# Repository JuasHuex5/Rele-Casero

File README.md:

# Rele Casero

Autor : Demian David Ramirez

---
# **Descripción**

Este proyecto tiene la finalidad de poder recrear un módulo Relé funcional para accionar un dispositivo electrónico que opera a un voltaje mucho mayor mediante una señal digital proveniente de un microcontrolador programable.
Un ejemplo concreto sería encender un foco, o iniciar una máquina más grande que funciona a 220v.

# **Funcionamiento**

El Esp32 recibe una señal inalámbrica y envía una señal eléctrica con dirección al relé. El sistema es separado por un optoacoplador el cual transmite esa señal sin comprometer al microcontrolador. El transistor se conecta en modo saturación para entregar el voltaje necesario para encender el relé.

# **Justificación de componentes**

### ESP32:
Este microcontrolador permite el fácil control de componentes por señales electrónicas, contando con la capacidad de comunicarse inalámbricamente.

### Relé:
Permite que una señal de menor intensidad encienda un dispositivo de mayor voltaje.

### Optoacoplador:
Aísla dos partes del circuito para evitar que un voltaje mayor queme la parte de bajo voltaje.

### Transistor:
El Relé sólo recibirá corriente cuando el Transistor permite el paso(Como medida preventiva para asegurar el curso correcto de la corriente).

# Analisis Economico
### Materiales

| Componente | Precio |
| ------------- | ------------- |
| ESP32 C3 super mini | 8500 |
| Relé | 1800  |
| 4n25(Optoacoplador) | 3844 |
|2n2222(Transistor) | 200 |
| XL6009 | 3608 - 2990 |
|Placa de cobre|880|

Precio Final:18214

# ESQUEMATICO

# PCB

# Objetivo
Se realiza este proyecto con la finalidad de poder armar un modulo Relay desde casa, ya que los que se encuentran en el mercado son mucho mas costosos que montandolo de manera casera.

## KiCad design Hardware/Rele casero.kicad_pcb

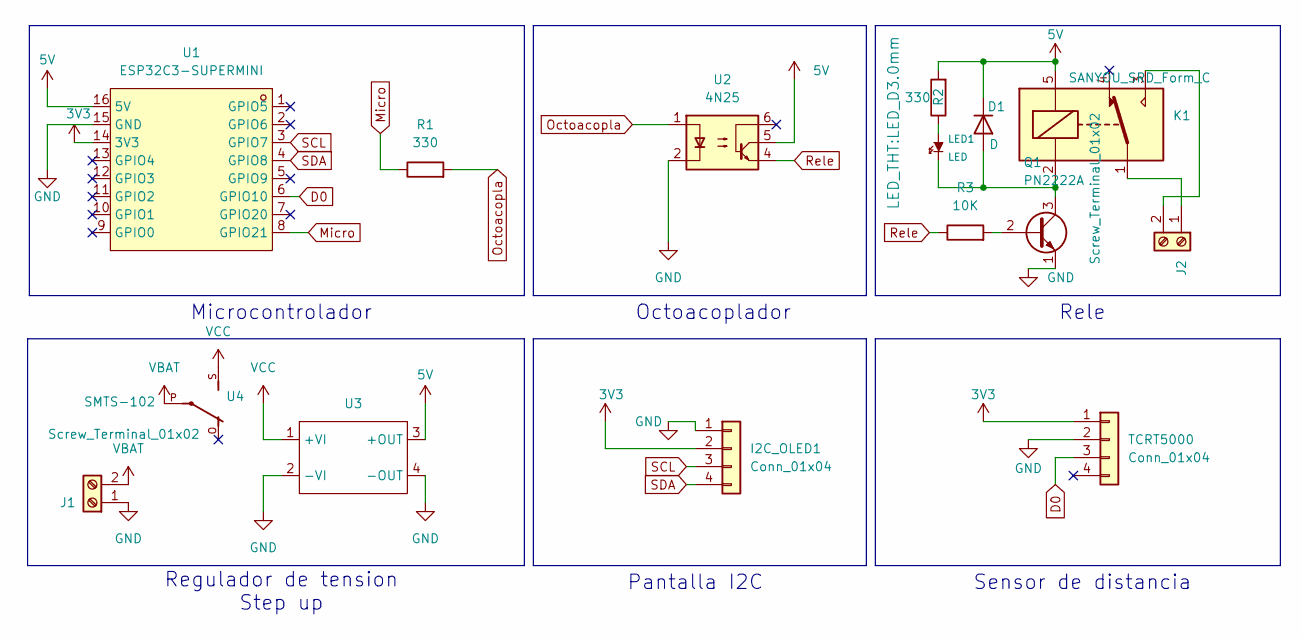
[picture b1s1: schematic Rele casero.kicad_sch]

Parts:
D1: D; D_A-405_P10.16mm_Horizontal
I2C_OLED1: Conn_01x04; PinSocket_1x04_P2.54mm_Vertical
J1, J2: Screw_Terminal_01x02; TerminalBlock_Phoenix_MKDS-1,5-2-5.08_1x02_P5.08mm_Horizont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
K1: SANYOU_SRD_Form_C; Relay_SPDT_SANYOU_SRD_Series_Form_C
LED1: LED; LED_D3.0mm
Q1: PN2222A; TO-92_Inline
R1, R2: 330; R_Axial_DIN0204_L3.6mm_D1.6mm_P7.62mm_Horizontal
R3: 10K; R_Axial_DIN0204_L3.6mm_D1.6mm_P7.62mm_Horizontal
TCRT5000: Conn_01x04; PinSocket_1x04_P2.54mm_Vertical
U1: ESP32C3-SUPERMINI; COMM-SMD_16P-L22.5-W18.0-P2.54-TL; MPN ESP32C3-SuperMini; LCSC Part C9900147397
U2: 4N25; DIP-6_W7.62mm
U3: MT3608-Module
U4: SMTS-102

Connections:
3V3: I2C_OLED1.2, TCRT5000.1, U1.14 (3V3)
5V: D1.1 (K), K1.5, R2.2, U1.16 (5V), U2.5, U3.3 (+OUT)
D0: TCRT5000.3, U1.6 (GPIO10)
GND: I2C_OLED1.1, J1.1, Q1.1 (E), TCRT5000.2, U1.15 (GND), U2.2, U3.2 (-VI), U3.4 (-OUT)
Micro: R1.1, U1.8 (GPIO21)
unnamed: D1.2 (A), K1.2, LED1.2 (K), Q1.3 (C)
unnamed: J2.1, K1.1
unnamed: J2.2, K1.3
unnamed: LED1.1 (A), R2.1
unnamed: Q1.2 (B), R3.2
Octoacopla: R1.2, U2.1
Rele: R3.1, U2.4
SCL: I2C_OLED1.3, U1.3 (GPIO7)
SDA: I2C_OLED1.4, U1.4 (GPIO8)
VBAT: J1.2, U4.P
VCC: U3.1 (+VI), U4.S

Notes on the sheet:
Microcontrolador
Regulador de tension Step up
Pantalla I2C
Sensor de distancia
Octoacoplador
Rele

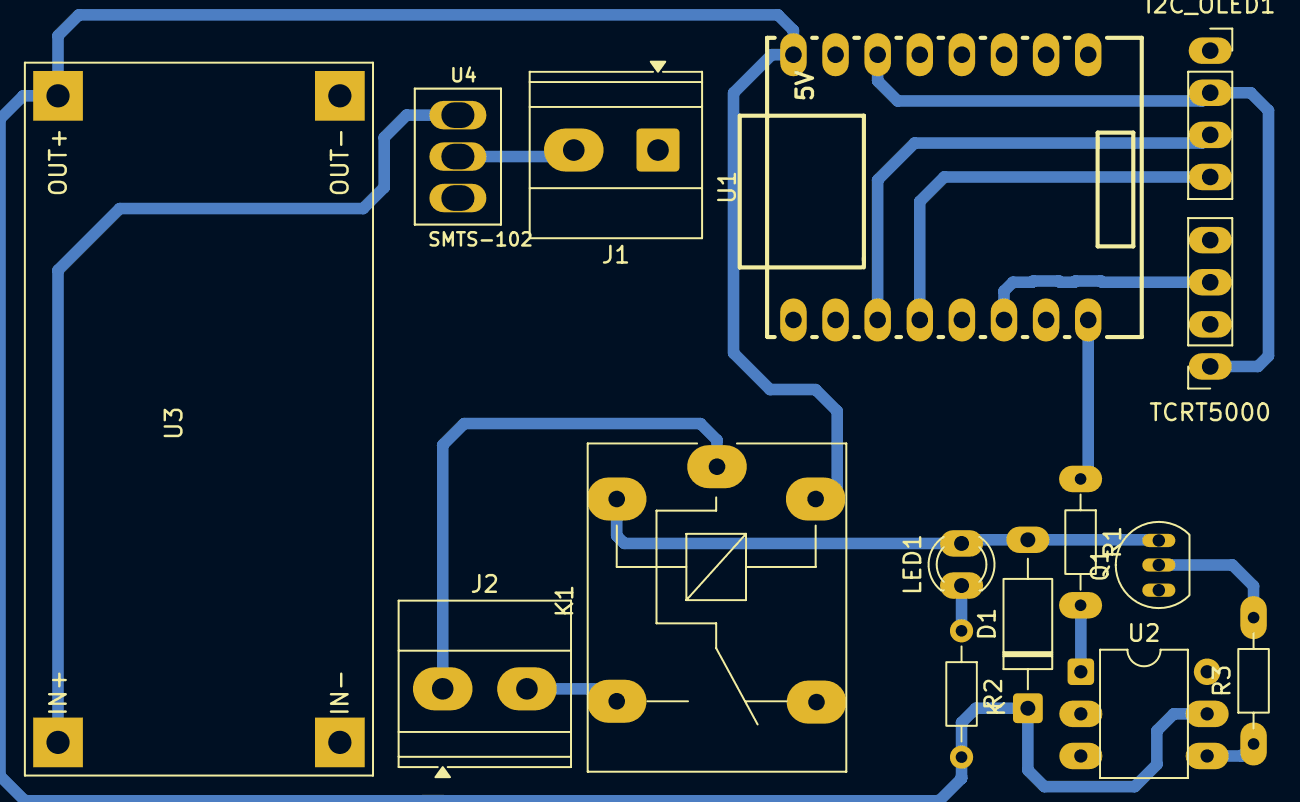
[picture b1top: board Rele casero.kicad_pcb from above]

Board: 2 copper layers, 15 parts (0 on the bottom side), 16 nets.
